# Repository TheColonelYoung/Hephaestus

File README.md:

# Hephaestus
Solder paste dispensor powered by stepper motor.

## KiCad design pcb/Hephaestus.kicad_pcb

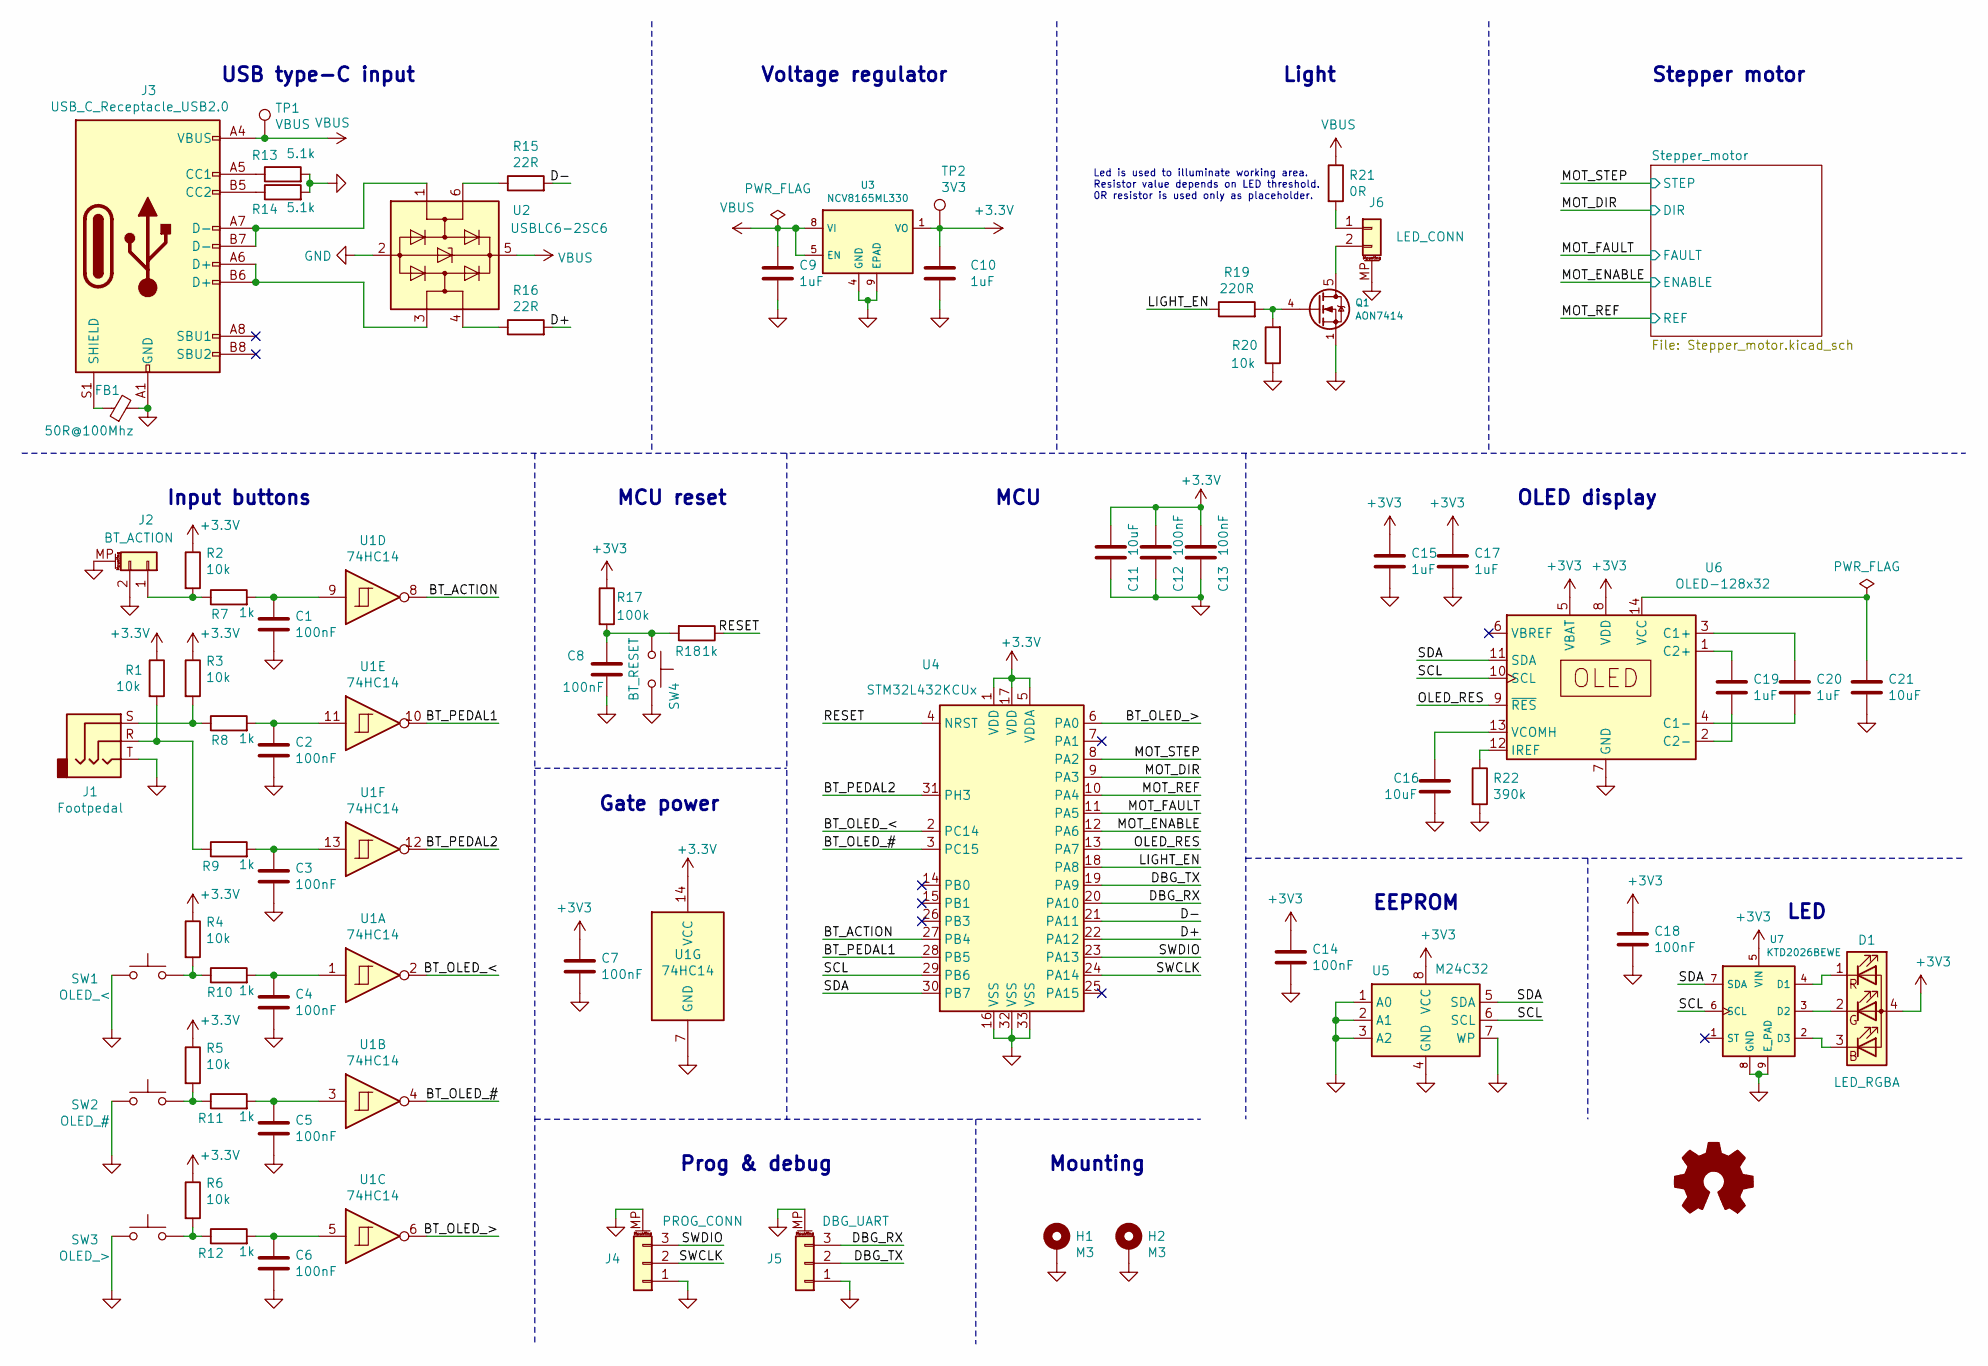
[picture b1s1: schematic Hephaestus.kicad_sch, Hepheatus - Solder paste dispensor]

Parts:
C1, C2, C3, C4, C5, C6, C7, C8, C12, C13, C14, C18: 100nF; C_0603_1608Metric
C9, C10, C15, C17, C19, C20: 1uF; C_0603_1608Metric
C11, C16, C21: 10uF; C_0805_2012Metric
D1: LED_RGBA; R_Array_Convex_2x0606
FB1: 50R@100Mhz; L_1206_3216Metric
H1, H2: M3; MountingHole_3.2mm_M3_Pad_Via
J1: Footpedal; Jack_3.5mm_CUI_SJ-3523-SMT_Horizontal
J2: BT_ACTION; Amphenol_10114830-11102LF_1x02_P1.25mm_Horizontal
J3: USB_C_Receptacle_USB2.0; USB_C_Receptacle_HRO_TYPE-C-31-M-12
J4: PROG_CONN; Amphenol_10114828-11103LF_1x03_P1.25mm_Vertical
J5: DBG_UART; Amphenol_10114828-11103LF_1x03_P1.25mm_Vertical
J6: LED_CONN; Amphenol_10114830-11102LF_1x02_P1.25mm_Horizontal
Q1: AON7414; DFN-8-1EP_3x3mm_P0.65mm_EP1.55x2.4mm
R1, R2, R3, R4, R5, R6, R20: 10k; R_0603_1608Metric
R7, R8, R9, R10, R11, R12, R18: 1k; R_0603_1608Metric
R13, R14: 5.1k; R_0603_1608Metric
R15, R16: 22R; R_0603_1608Metric
R17: 100k; R_0603_1608Metric
R19: 220R; R_0603_1608Metric
R21: 0R; R_1206_3216Metric
R22: 390k; R_0603_1608Metric
SW1: OLED_<; SW_SPST_TL3305A
SW2: OLED_#; SW_SPST_TL3305A
SW3: OLED_>; SW_SPST_TL3305A
SW4: BT_RESET; KMT031NGJLHS
TP1: VBUS; TestPoint_Pad_D0.5mm
TP2: 3V3; TestPoint_Pad_D0.5mm
U1: 74HC14; Texas_S-PVQFN-N14
U2: USBLC6-2SC6; SOT-23-6
U3: NCV8165ML330; DFN-8-1EP_3x3mm_P0.65mm_EP1.55x2.4mm
U4: STM32L432KCUx; QFN-32-1EP_5x5mm_P0.5mm_EP3.45x3.45mm
U5: M24C32; DFN-8-1EP_3x2mm_P0.5mm_EP1.3x1.5mm
U6: OLED-128x32; OLED_128x32
U7: KTD2026BEWE; UTDFN-8-1EP_1.5x1.5mm_P0.4mm_EP0.8x1.45mm

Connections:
/BT_ACTION: U1.8, U4.27 (PB4)
/BT_OLED_#: U1.4, U4.3 (PC15)
/BT_OLED_<: U1.2, U4.2 (PC14)
/BT_OLED_>: U1.6, U4.6 (PA0)
/BT_PEDAL1: U1.10, U4.28 (PB5)
/BT_PEDAL2: U1.12, U4.31 (PH3)
/D+: R16.2, U4.22 (PA12)
/D-: R15.2, U4.21 (PA11)
/DBG_RX: J5.3, U4.20 (PA10)
/DBG_TX: J5.2, U4.19 (PA9)
/LIGHT_EN: R19.1, U4.18 (PA8)
/MOT_DIR: U4.9 (PA3); also elsewhere on the board
/MOT_ENABLE: U4.12 (PA6); also elsewhere on the board
/MOT_FAULT: U4.11 (PA5); also elsewhere on the board
/MOT_REF: U4.10 (PA4); also elsewhere on the board
/MOT_STEP: U4.8 (PA2); also elsewhere on the board
/OLED_RES: U4.13 (PA7), U6.9 (~RES)
/RESET: R18.1, U4.4 (NRST)
/SCL: U4.29 (PB6), U5.6 (SCL), U6.10 (SCL), U7.6 (SCL)
/SDA: U4.30 (PB7), U5.5 (SDA), U6.11 (SDA), U7.7 (SDA)
/SWCLK: J4.2, U4.24 (PA14)
/SWDIO: J4.3, U4.23 (PA13)
GND: C1.2, C2.2, C3.2, C4.2, C5.2, C6.2, C7.2, C8.2, C9.2, C10.2, C11.2, C12.2, C13.2, C14.2, C15.2, C16.2, C17.2, C18.2, C21.2, FB1.2, H1.1, H2.1, J1.T, J2.2, J2.MP (MountPin), J3.A1 (GND), J3.A12 (GND), J3.B1 (GND), J3.B12 (GND), J4.1, J4.MP (MountPin), J5.1, J5.MP (MountPin), J6.MP (MountPin), Q1.1 (S), Q1.2 (S), Q1.3 (S), R13.2, R14.2, R20.1, R22.2, SW1.1, SW2.1, SW3.1, SW4.2, U1.7 (GND), U2.2 (GND), U3.4 (GND), U3.9 (EPAD), U4.16 (VSS), U4.32 (VSS), U4.33 (VSS), U5.1 (A0), U5.2 (A1), U5.3 (A2), U5.4 (GND), U5.7 (WP), U6.7 (GND), U7.8 (GND), U7.9 (E_PAD); also elsewhere on the board
unnamed: C1.1, R7.2, U1.9
unnamed: C2.1, R8.2, U1.11
unnamed: C3.1, R9.2, U1.13
unnamed: C4.1, R10.2, U1.1
unnamed: C5.1, R11.2, U1.3
unnamed: C6.1, R12.2, U1.5
unnamed: C8.1, R17.2, R18.2, SW4.1
unnamed: C16.1, U6.13 (VCOMH)
unnamed: C19.1, U6.1 (C2+)
unnamed: C19.2, U6.2 (C2-)
unnamed: C20.1, U6.3 (C1+)
unnamed: C20.2, U6.4 (C1-)
unnamed: C21.1, U6.14 (VCC)
unnamed: D1.1 (RK), U7.4 (D1)
unnamed: D1.2 (GK), U7.3 (D2)
unnamed: D1.3 (BK), U7.2 (D3)
unnamed: FB1.1, J3.S1 (SHIELD)
unnamed: J1.R, R1.2, R9.1
unnamed: J1.S, R3.2, R8.1
unnamed: J3.A5 (CC1), R13.1
unnamed: J3.A6 (D+), J3.B6 (D+), U2.3 (I/O2)
unnamed: J3.A7 (D-), J3.B7 (D-), U2.1 (I/O1)
unnamed: J3.B5 (CC2), R14.1
unnamed: J6.1, R21.2
unnamed: J6.2, Q1.5 (D), Q1.6 (D), Q1.7 (D), Q1.8 (D), Q1.9 (D)
unnamed: Q1.4 (G), R19.2, R20.2
unnamed: J2.1, R2.2, R7.1
unnamed: R4.2, R10.1, SW1.2
unnamed: R5.2, R11.1, SW2.2
unnamed: R6.2, R12.1, SW3.2
unnamed: R15.1, U2.6 (I/O1)
unnamed: R16.1, U2.4 (I/O2)
unnamed: R22.1, U6.12 (IREF)
VBUS: C9.1, J3.A4 (VBUS), J3.A9 (VBUS), J3.B4 (VBUS), J3.B9 (VBUS), R21.1, TP1.1, U2.5 (VBUS), U3.5 (EN), U3.8 (VI); also elsewhere on the board
no_connect_73: J3.A8 (SBU1)
no_connect_74: J3.B8 (SBU2)
no_connect_75: U4.14 (PB0)
no_connect_76: U4.15 (PB1)
no_connect_77: U4.25 (PA15)
no_connect_78: U4.26 (PB3)
no_connect_79: U4.7 (PA1)
no_connect_80: U6.6 (VBREF)
no_connect_81: U7.1 (ST)

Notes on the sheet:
Input buttons
USB type-C input
Gate power
MCU reset
Prog & debug
Voltage regulator
MCU
Mounting
Led is used to illuminate working area. Resistor value depends on LED threshold. 0R resistor is used only as placeholder.
Light
EEPROM
OLED display
Stepper motor
LED

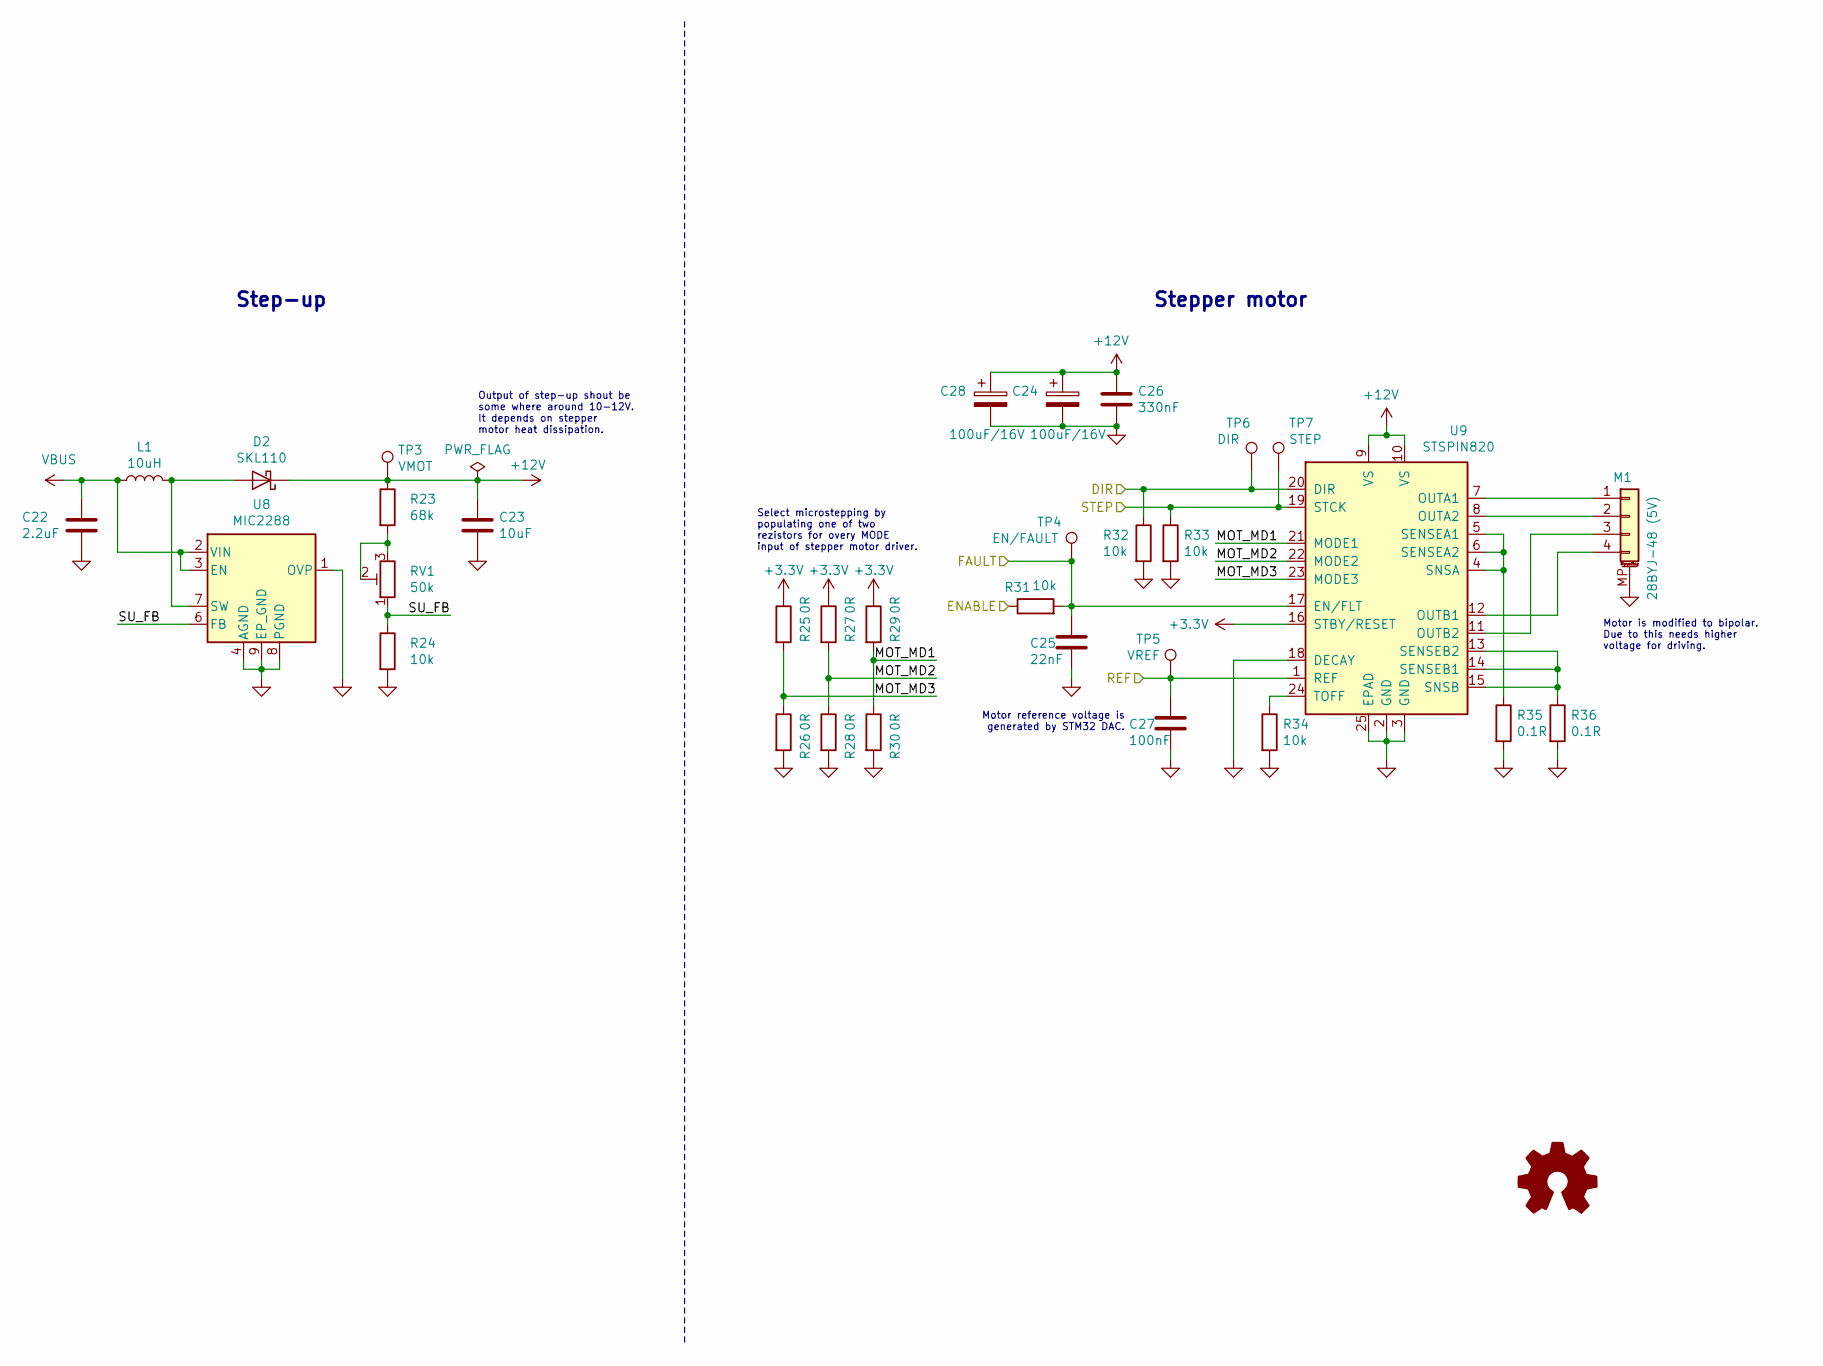
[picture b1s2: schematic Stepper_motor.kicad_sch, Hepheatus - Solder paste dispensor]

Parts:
C22: 2.2uF; C_0603_1608Metric
C23: 10uF; C_0805_2012Metric
C24, C28: 100uF/16V; CP_EIA-7343-30_AVX-N
C25: 22nF; C_0603_1608Metric
C26: 330nF; C_0603_1608Metric
C27: 100nF; C_0603_1608Metric
D2: SKL110; D_SOD-123F
L1: 10uH; Laird_2520
M1: 28BYJ-48 (5V); Amphenol_10114830-11103LF_1x04_P1.25mm_Horizontal
R23: 68k; R_0603_1608Metric
R24, R31, R32, R33, R34: 10k; R_0603_1608Metric
R25, R26, R27, R28, R29, R30: 0R; R_0603_1608Metric
R35, R36: 0.1R; R_1206_3216Metric
RV1: 50k; Potentiometer_Bourns_3214J_Horizontal
TP3: VMOT; TestPoint_Pad_D0.5mm
TP4: EN/FAULT; TestPoint_Pad_D0.5mm
TP5: VREF; TestPoint_Pad_D0.5mm
TP6: DIR; TestPoint_Pad_D0.5mm
TP7: STEP; TestPoint_Pad_D0.5mm
U8: MIC2288; Micrel_MLF-8-1EP_2x2mm_P0.5mm_EP0.8x1.3mm_ThermalVias
U9: STSPIN820; QFN-24-1EP_4x4mm_P0.5mm_EP2.65x2.65mm_ThermalVias

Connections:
+12V: C23.1, C24.1, C26.1, C28.1, D2.1 (K), R23.1, TP3.1, U9.9 (VS), U9.10 (VS)
/MOT_DIR: R32.1, TP6.1, U9.20 (DIR); also elsewhere on the board
/MOT_ENABLE: R31.1; also elsewhere on the board
/MOT_FAULT: C25.1, R31.2, TP4.1, U9.17 (EN/FLT); also elsewhere on the board
/MOT_REF: C27.1, TP5.1, U9.1 (REF); also elsewhere on the board
/MOT_STEP: R33.1, TP7.1, U9.19 (STCK); also elsewhere on the board
/Stepper_motor/MOT_MD1: R29.2, R30.1, U9.21 (MODE1)
/Stepper_motor/MOT_MD2: R27.2, R28.1, U9.22 (MODE2)
/Stepper_motor/MOT_MD3: R25.2, R26.1, U9.23 (MODE3)
/Stepper_motor/SU_FB: R24.1, RV1.1, U8.6 (FB)
GND: C22.2, C23.2, C24.2, C25.2, C26.2, C27.2, C28.2, M1.MP (MountPin), R24.2, R26.2, R28.2, R30.2, R32.2, R33.2, R34.2, R35.2, R36.2, U8.1 (OVP), U8.4 (AGND), U8.8 (PGND), U8.9 (EP_GND), U9.2 (GND), U9.3 (GND), U9.18 (DECAY), U9.25 (EPAD); also elsewhere on the board
unnamed: D2.2 (A), L1.2, U8.7 (SW)
unnamed: R23.2, RV1.2, RV1.3
unnamed: R34.1, U9.24 (TOFF)
unnamed: R35.1, U9.4 (SNSA), U9.5 (SENSEA1), U9.6 (SENSEA2)
unnamed: R36.1, U9.13 (SENSEB2), U9.14 (SENSEB1), U9.15 (SNSB)
unnamed: M1.1, U9.7 (OUTA1)
unnamed: M1.2, U9.8 (OUTA2)
unnamed: M1.3, U9.11 (OUTB2)
unnamed: M1.4, U9.12 (OUTB1)
VBUS: C22.1, L1.1, U8.2 (VIN), U8.3 (EN); also elsewhere on the board
no_connect_82: U8.5 (NC)

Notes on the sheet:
Step-up
Output of step-up shout be some where around 10-12V. It depends on stepper motor heat dissipation.
Select microstepping by populating one of two rezistors for overy MODE input of stepper motor driver.
Motor reference voltage is generated by STM32 DAC.
Stepper motor
Motor is modified to bipolar. Due to this needs higher voltage for driving.

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
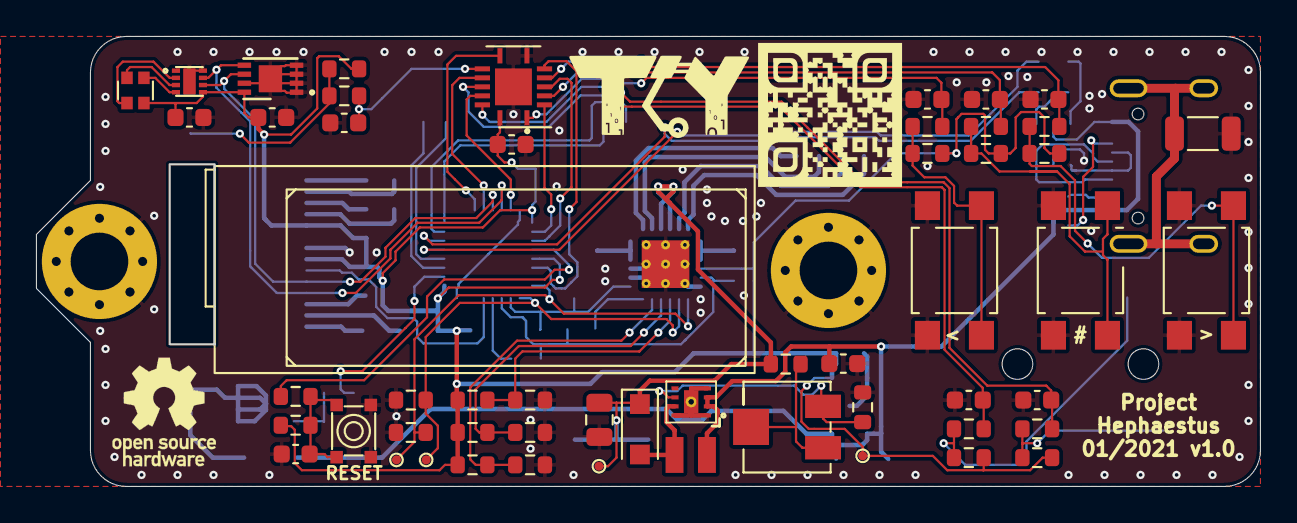
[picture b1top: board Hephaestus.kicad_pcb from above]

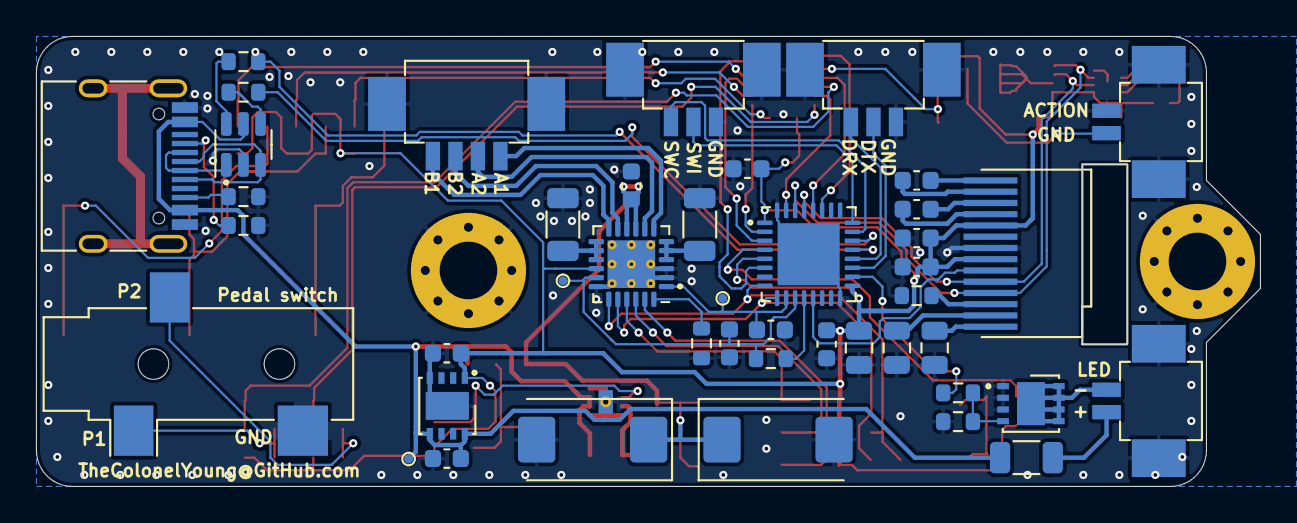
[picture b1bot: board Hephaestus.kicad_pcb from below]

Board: 2 copper layers, 68.0 x 25.0 mm, 99 parts (43 on the bottom side), 72 nets.

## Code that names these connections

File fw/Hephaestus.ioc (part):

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Mcu.UserName=STM32L432KCUx
PA0.GPIO_Label=BT_PEDAL2
PH3-BOOT0.GPIO_Label=BT_OLED_>
PA11.Mode=Device
PA3.GPIOParameters=GPIO_Label
PA6.GPIO_Label=MOT_FAULT
PA2.GPIOParameters=GPIO_Label
RCC.SYSCLKSource=RCC_SYSCLKSOURCE_PLLCLK
PB5.GPIOParameters=GPIO_Label
PA14\ (JTCK-SWCLK).Signal=SYS_JTCK-SWCLK
PA12.Signal=USB_DP
PC15-OSC32_OUT\ (PC15).GPIOParameters=GPIO_Label
PB6.Signal=I2C1_SCL
PB6.Mode=I2C
PA8.GPIOParameters=GPIO_Label
RCC.HSE_VALUE=8000000
PH3-BOOT0.GPIOParameters=GPIO_Label
PB7.Signal=I2C1_SDA
PA8.Signal=GPIO_Output
PA0.Signal=GPXTI0
PH3-BOOT0.Signal=GPXTI3
Mcu.Package=UFQFPN32
PA6.Signal=GPXTI6
PA2.GPIO_Label=MOT_STEP
PA10.Signal=USART1_RX
PA5.GPIOParameters=GPIO_Label
PB5.GPIO_Label=BT_PEDAL1
PA13\ (JTMS-SWDIO).Signal=SYS_JTMS-SWDIO
PA3.Signal=GPIO_Output
PA6.GPIOParameters=GPIO_Label
PA14\ (JTCK-SWCLK).Mode=Serial_Wire
PC15-OSC32_OUT\ (PC15).GPIO_Label=BT_OLED_\#
PA10.Mode=Asynchronous
PC15-OSC32_OUT\ (PC15).Signal=GPXTI15
PC14-OSC32_IN\ (PC14).GPIO_Label=BT_OLED_<
PA9.Mode=Asynchronous
PB4\ (NJTRST).GPIOParameters=GPIO_Label
PA8.GPIO_Label=LIGHT_EN
PA9.Signal=USART1_TX
PA5.Signal=GPIO_Output
board=custom
Mcu.Name=STM32L432K(B-C)Ux
PA2.Signal=S_TIM15_CH1
PA13\ (JTMS-SWDIO).Mode=Serial_Wire
PA4.Signal=COMP_DAC11_group
RCC.SYSCLKFreq_VALUE=80000000
PB5.Signal=GPXTI5
PA7.GPIO_Label=OLED_RES
PA12.Mode=Device
PA5.GPIO_Label=MOT_ENABLE
PC14-OSC32_IN\ (PC14).Signal=GPXTI14
PB7.Mode=I2C
PA11.Signal=USB_DM
PA0.GPIOParameters=GPIO_Label
PC14-OSC32_IN\ (PC14).GPIOParameters=GPIO_Label
PB4\ (NJTRST).GPIO_Label=BT_ACTION
PA7.GPIOParameters=GPIO_Label
PA3.GPIO_Label=MOT_DIR
PA7.Signal=GPIO_Output
PB4\ (NJTRST).Signal=GPXTI4

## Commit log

2021-01-27 Schema: initial component placement
2021-01-27 CubeMX project initialization
2021-01-28 Add gitignore and remove KiCAD backups
2021-01-28 Schema: add in put buttons and denoising
2021-01-28 Schema: add light connector
2021-01-29 Schema: change stepper motor driver to STPSIN820, add step-up convertor
2021-01-29 FW: update MCu connections to button and stepper motor
2021-01-29 Schema: connect MCU to buttons and stepper motor
2021-01-29 Schema & PCB: add page layout
2021-01-29 PCB: initial component placing and sketch board dimensions
2021-02-01 PCB: Basic routing done
2021-02-01 FW: update MCU pin connections (Input buttons)
2021-02-02 PCB: add silkscreen marking
